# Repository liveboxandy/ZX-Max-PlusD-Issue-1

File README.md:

This is a recreation of the ZX Max Plus D Issue 1 PCB as designed by DonSuperfo but done in KiCAD 10.

This was only done in order to create an interactive BOM (in the BOM folder) to assist in the assembling of the PCB.

The KiCAD schematics 'should' be correct but nothing should be assumed as correct without checking with the original schematic and PCB layout. Although I have followed the original track and via layout further checking should be done before using these files to order a pcb with. Currently I would still order the pcb from PCBWay using the link from https://github.com/DonSuperfo/ZX-Max-128

Note that any part number for any device used in this project might not be the correct one from the original BOM as supplied from PCBWay as I had to change some parts to get a footprint that would fit in the space on the original pcb with the correct pin spacing. This required selecting a different part number or vendor. This applies mainly to capacitors. Some other parts are no longer available under that number from Digikey.

As always, measure twice and order one.

Use at your own risk.

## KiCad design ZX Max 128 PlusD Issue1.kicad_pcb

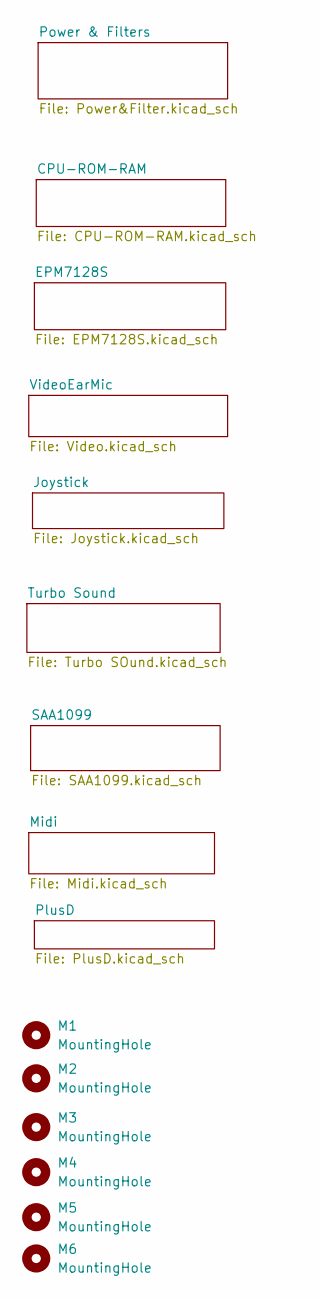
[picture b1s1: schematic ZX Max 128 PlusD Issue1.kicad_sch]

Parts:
M1, M2, M3, M4, M5, M6: MountingHole; MountingHole_3.2mm_M3_DIN965

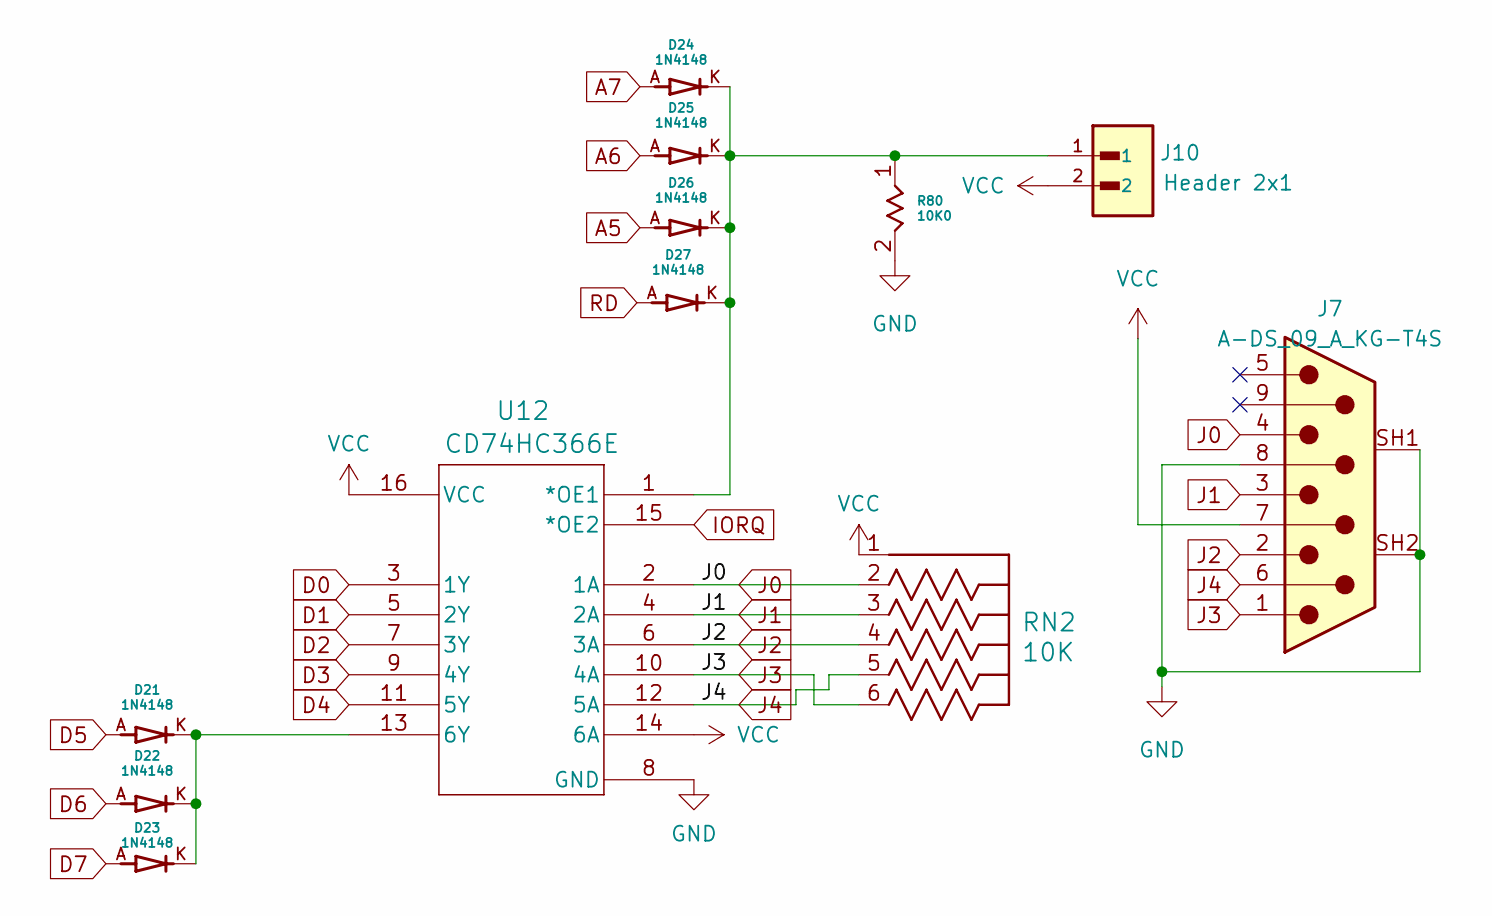
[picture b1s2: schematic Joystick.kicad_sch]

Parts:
D21, D22, D23, D24, D25, D26, D27: 1N4148; DIOAD753W49L380D172B; PARTREV 5
J7: A-DS_09_A_KG-T4S; ASSMANN_A-DS_09_A_KG-T4S; PARTREV 10
J10: Header 2x1; HARWIN_M20-9990246; PARTREV 14
R80: 10K0; STA_CF14_STP
RN2: 10K; 4606X-101-103LF
U12: CD74HC366E

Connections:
A5: D26.A; also elsewhere on the board
A6: D25.A; also elsewhere on the board
A7: D24.A; also elsewhere on the board
D0: U12.3 (1Y); also elsewhere on the board
D1: U12.5 (2Y); also elsewhere on the board
D2: U12.7 (3Y); also elsewhere on the board
D3: U12.9 (4Y); also elsewhere on the board
D4: U12.11 (5Y); also elsewhere on the board
D5: D21.A; also elsewhere on the board
D6: D22.A; also elsewhere on the board
D7: D23.A; also elsewhere on the board
GND: J7.8, J7.SH1, J7.SH2, R80.2, U12.8 (GND); also elsewhere on the board
IORQ: U12.15 (*OE2); also elsewhere on the board
J0: J7.4, RN2.2, U12.2 (1A)
J1: J7.3, RN2.3, U12.4 (2A)
J2: J7.2, RN2.4, U12.6 (3A)
J3: J7.1, RN2.6, U12.10 (4A)
J4: J7.6, RN2.5, U12.12 (5A)
unnamed: D21.K, D22.K, D23.K, U12.13 (6Y)
unnamed: D24.K, D25.K, D26.K, D27.K, J10.1, R80.1, U12.1 (*OE1)
RD: D27.A; also elsewhere on the board
VCC: J7.7, J10.2, RN2.1, U12.14 (6A), U12.16 (VCC); also elsewhere on the board

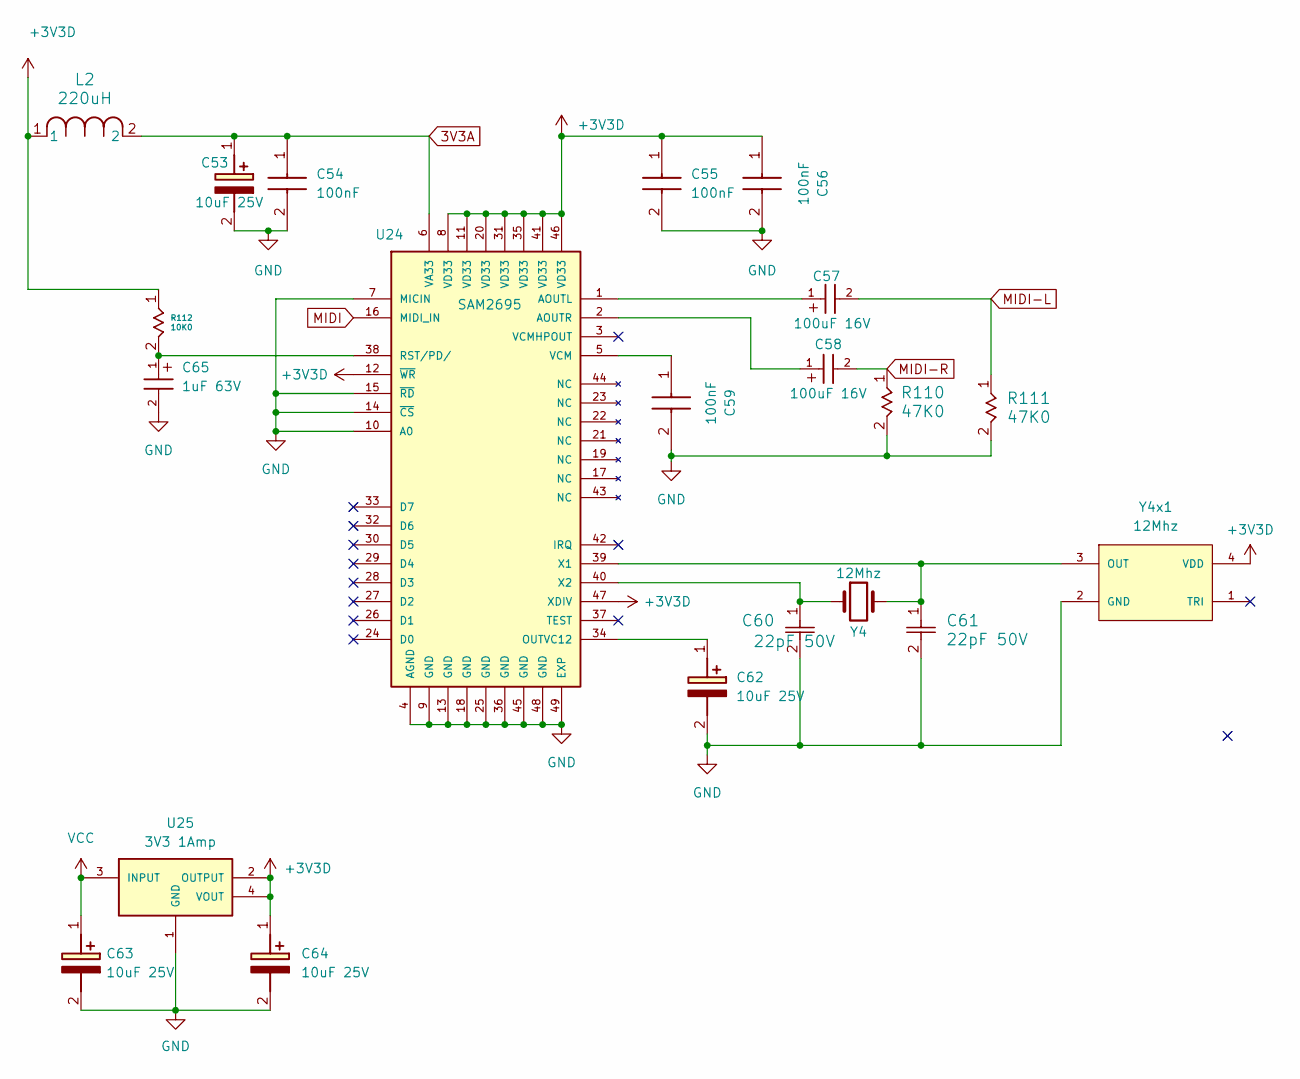
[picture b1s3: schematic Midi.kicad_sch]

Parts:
C53, C62, C63, C64: 10uF 25V; CAPPRD200W50D500H1100; Mouser Part Number 667-ECA-1EM100B
C54, C55, C56, C59: 100nF; CAPRB250W50L400T250H550; Mouser Part Number 594-K104Z15Y5VF5TL2
C57, C58: 100uF 16V; WCAP-ATG8_5X11_DXL_
C60, C61: 22pF 50V; CAP_K220J15C0GF53L2_VIS
C65: 1uF 63V; WCAP-ATG5_5X11_DXL_
L2: 220uH; IND_BOURNS_RLB0608
R110, R111: 47K0; STA_CF14_STP
R112: 10K0; STA_CF14_STP
U24: SAM2695; QFN40P600X600X90-49N; PARTREV N/A
U25: 3V3 1Amp; SOT230P700X185-4N
Y4: 12Mhz; Crystal_HC49-4H_Vertical
Y4x1: 12Mhz; OSC_ECS-2333-120-BN-TR

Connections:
3V3A: C53.1 (+), C54.1 (+), L2.2, U24.6 (VA33)
+3V3D: C55.1 (+), C56.1 (+), C64.1 (+), L2.1, R112.1, U24.8 (VD33), U24.11 (VD33), U24.12 (~WR), U24.20 (VD33), U24.31 (VD33), U24.35 (VD33), U24.41 (VD33), U24.46 (VD33), U24.47 (XDIV), U25.2 (OUTPUT), U25.4 (VOUT), Y4x1.4 (VDD); also elsewhere on the board
GND: C53.2 (-), C54.2 (-), C55.2 (-), C56.2 (-), C59.2 (-), C60.2, C61.2, C62.2 (-), C63.2 (-), C64.2 (-), C65.2, R110.2, R111.2, U24.4 (AGND), U24.7 (MICIN), U24.9 (GND), U24.10 (A0), U24.13 (GND), U24.14 (~CS), U24.15 (~RD), U24.18 (GND), U24.25 (GND), U24.36 (GND), U24.45 (GND), U24.48 (GND), U24.49 (EXP), U25.1 (GND), Y4x1.2 (GND); also elsewhere on the board
MIDI: U24.16 (MIDI_IN); also elsewhere on the board
MIDI-L: C57.2, R111.1; also elsewhere on the board
MIDI-R: C58.2, R110.1; also elsewhere on the board
unnamed: C59.1 (+), U24.5 (VCM)
unnamed: C62.1 (+), U24.34 (OUTVC12)
unnamed: C57.1, U24.1 (AOUTL)
unnamed: C58.1, U24.2 (AOUTR)
unnamed: C65.1, R112.2, U24.38 (RST/PD/)
unnamed: C61.1, U24.39 (X1), Y4.2, Y4x1.3 (OUT)
unnamed: C60.1, U24.40 (X2), Y4.1
VCC: C63.1 (+), U25.3 (INPUT); also elsewhere on the board

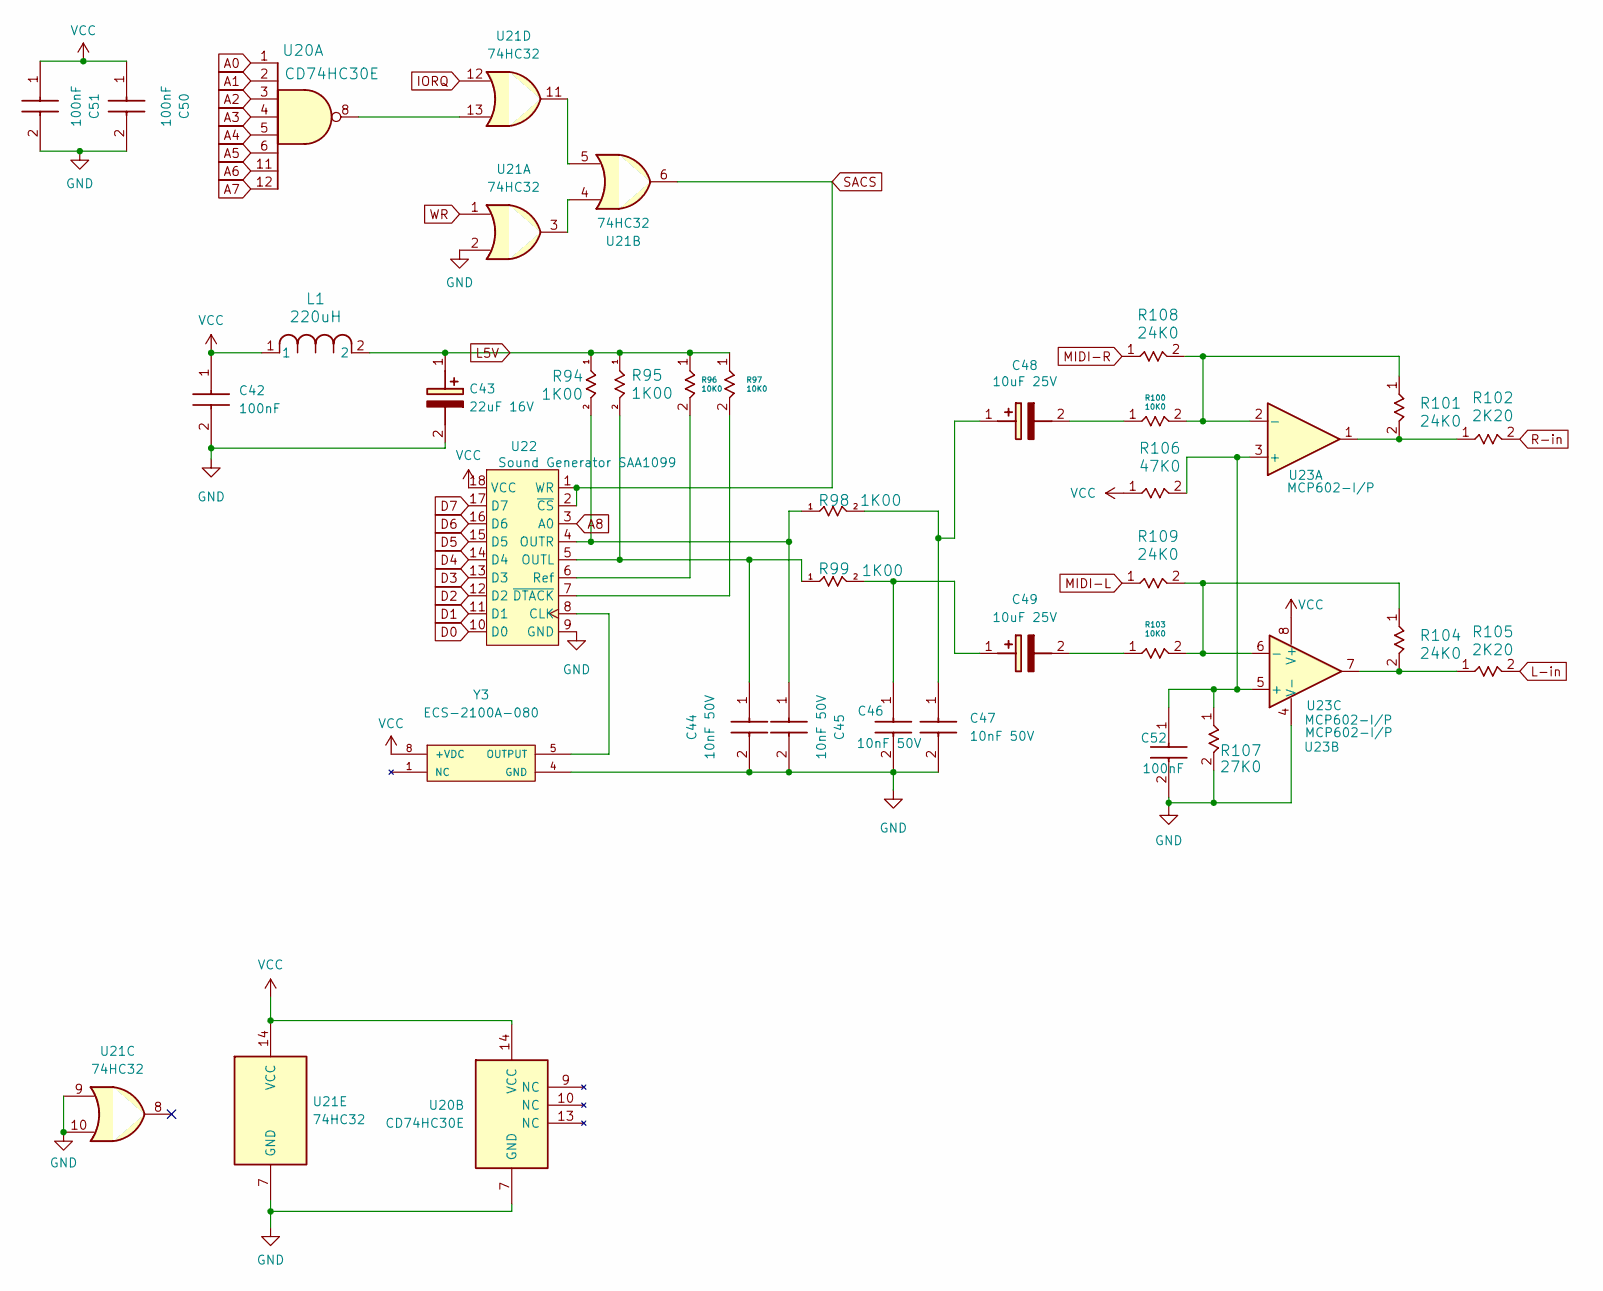
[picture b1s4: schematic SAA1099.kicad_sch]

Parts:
C42, C50, C51, C52: 100nF; CAPRB250W50L400T250H550; Mouser Part Number 594-K104Z15Y5VF5TL2
C43: 22uF 16V; CAPPRD200W50D500H1100; Mouser Part Number 667-ECA-1EM100B
C44, C45, C46, C47: 10nF 50V; CAPRB250W50L400T250H550; Mouser Part Number 594-K104Z15Y5VF5TL2
C48, C49: 10uF 25V; CAPPRD200W50D500H1100; Mouser Part Number 667-ECA-1EM100B
L1: 220uH; IND_BOURNS_RLB0608
R94, R95, R98, R99: 1K00; STA_CF14_STP
R96, R97, R100, R103: 10K0; STA_CF14_STP
R101, R104, R108, R109: 24K0; STA_CF14_STP
R102, R105: 2K20; STA_CF14_STP
R106: 47K0; STA_CF14_STP
R107: 27K0; STA_CF14_STP
U20: CD74HC30E; DIP794W53P254L1930H508Q14N
U21: 74HC32; DIP794W53P254L1930H508Q14N
U22: Sound Generator SAA1099; DIP-18_W7.62mm_Socket
U23: MCP602-I/P; DIP-8_W7.62mm_Socket
Y3: ECS-2100A-080; OSC_ECS-2100A-080; PARTREV N/A

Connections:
A0: U20.1; also elsewhere on the board
A1: U20.2; also elsewhere on the board
A2: U20.3; also elsewhere on the board
A3: U20.4; also elsewhere on the board
A4: U20.5; also elsewhere on the board
A5: U20.6; also elsewhere on the board
A6: U20.11; also elsewhere on the board
A7: U20.12; also elsewhere on the board
A8: U22.3 (A0); also elsewhere on the board
D0: U22.10 (D0); also elsewhere on the board
D1: U22.11 (D1); also elsewhere on the board
D2: U22.12 (D2); also elsewhere on the board
D3: U22.13 (D3); also elsewhere on the board
D4: U22.14 (D4); also elsewhere on the board
D5: U22.15 (D5); also elsewhere on the board
D6: U22.16 (D6); also elsewhere on the board
D7: U22.17 (D7); also elsewhere on the board
GND: C42.2 (-), C43.2 (-), C44.2 (-), C45.2 (-), C46.2 (-), C47.2 (-), C50.2 (-), C51.2 (-), C52.2 (-), R107.2, U20.7 (GND), U21.2, U21.7 (GND), U21.9, U21.10, U22.9 (GND), U23.4 (V-), Y3.4 (GND); also elsewhere on the board
IORQ: U21.12; also elsewhere on the board
L5V: C43.1 (+), L1.2, R94.1, R95.1, R96.1, R97.1
L-in: R105.2; also elsewhere on the board
MIDI-L: R109.1; also elsewhere on the board
MIDI-R: R108.1; also elsewhere on the board
unnamed: C44.1 (+), R95.2, R99.1, U22.5 (OUTL)
unnamed: C45.1 (+), R94.2, R98.1, U22.4 (OUTR)
unnamed: C46.1 (+), C49.1 (+), R99.2
unnamed: C47.1 (+), C48.1 (+), R98.2
unnamed: C48.2 (-), R100.1
unnamed: C49.2 (-), R103.1
unnamed: C52.1 (+), R106.2, R107.1, U23.3 (+), U23.5 (+)
unnamed: R101.2, R102.1, U23.1
unnamed: R104.2, R105.1, U23.7
unnamed: U20.8, U21.13
unnamed: U21.3, U21.4
unnamed: U21.5, U21.11
unnamed: U22.8 (CLK), Y3.5 (OUTPUT)
unnamed: R96.2, U22.6 (Ref)
unnamed: R97.2, U22.7 (~DTACK)
unnamed: R100.2, R101.1, R108.2, U23.2 (-)
unnamed: R103.2, R104.1, R109.2, U23.6 (-)
R-in: R102.2; also elsewhere on the board
SACS: U21.6, U22.1 (WR), U22.2 (~CS)
VCC: C42.1 (+), C50.1 (+), C51.1 (+), L1.1, R106.1, U20.14 (VCC), U21.14 (VCC), U22.18 (VCC), U23.8 (V+), Y3.8 (+VDC); also elsewhere on the board
WR: U21.1; also elsewhere on the board

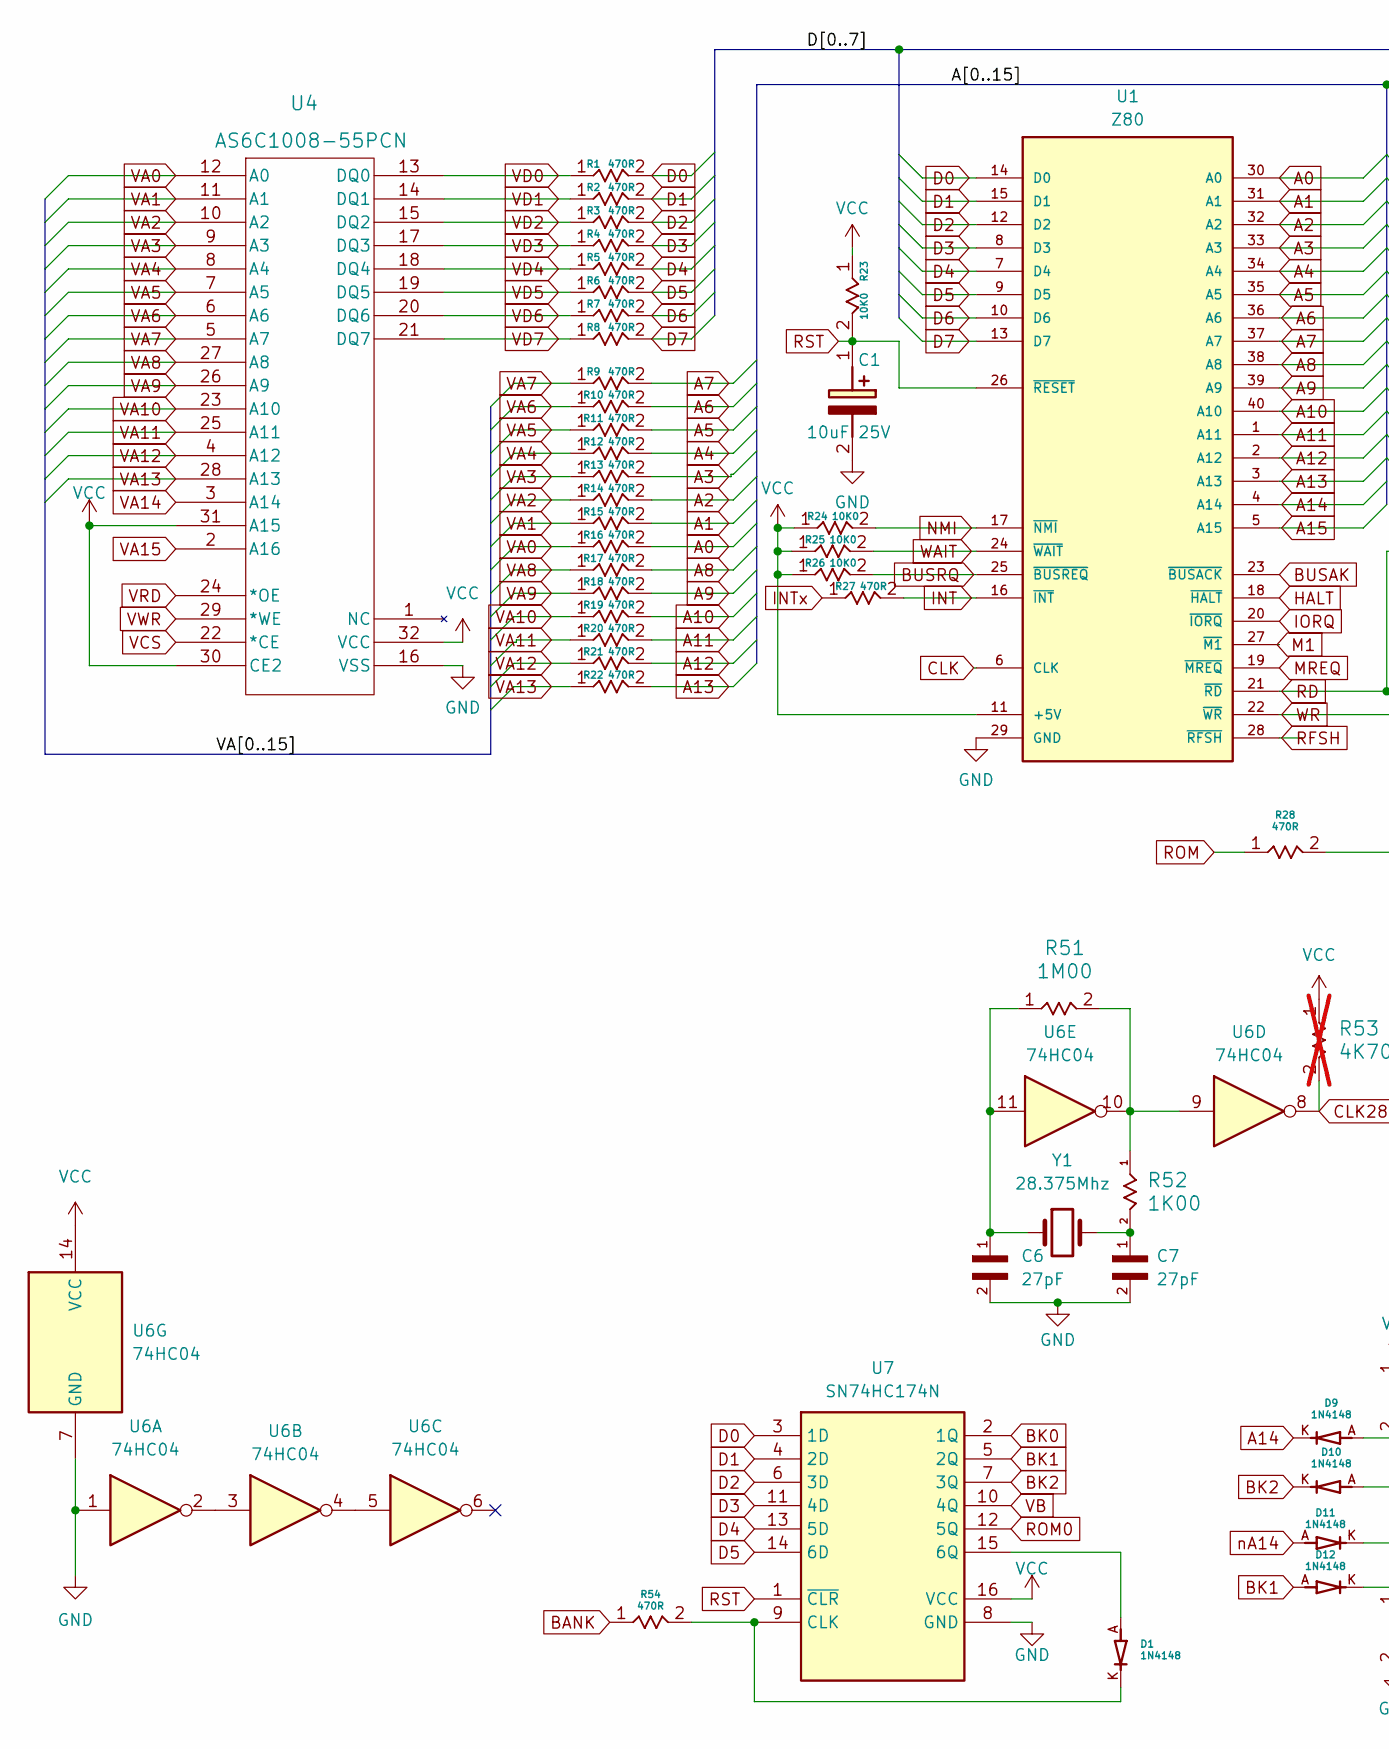
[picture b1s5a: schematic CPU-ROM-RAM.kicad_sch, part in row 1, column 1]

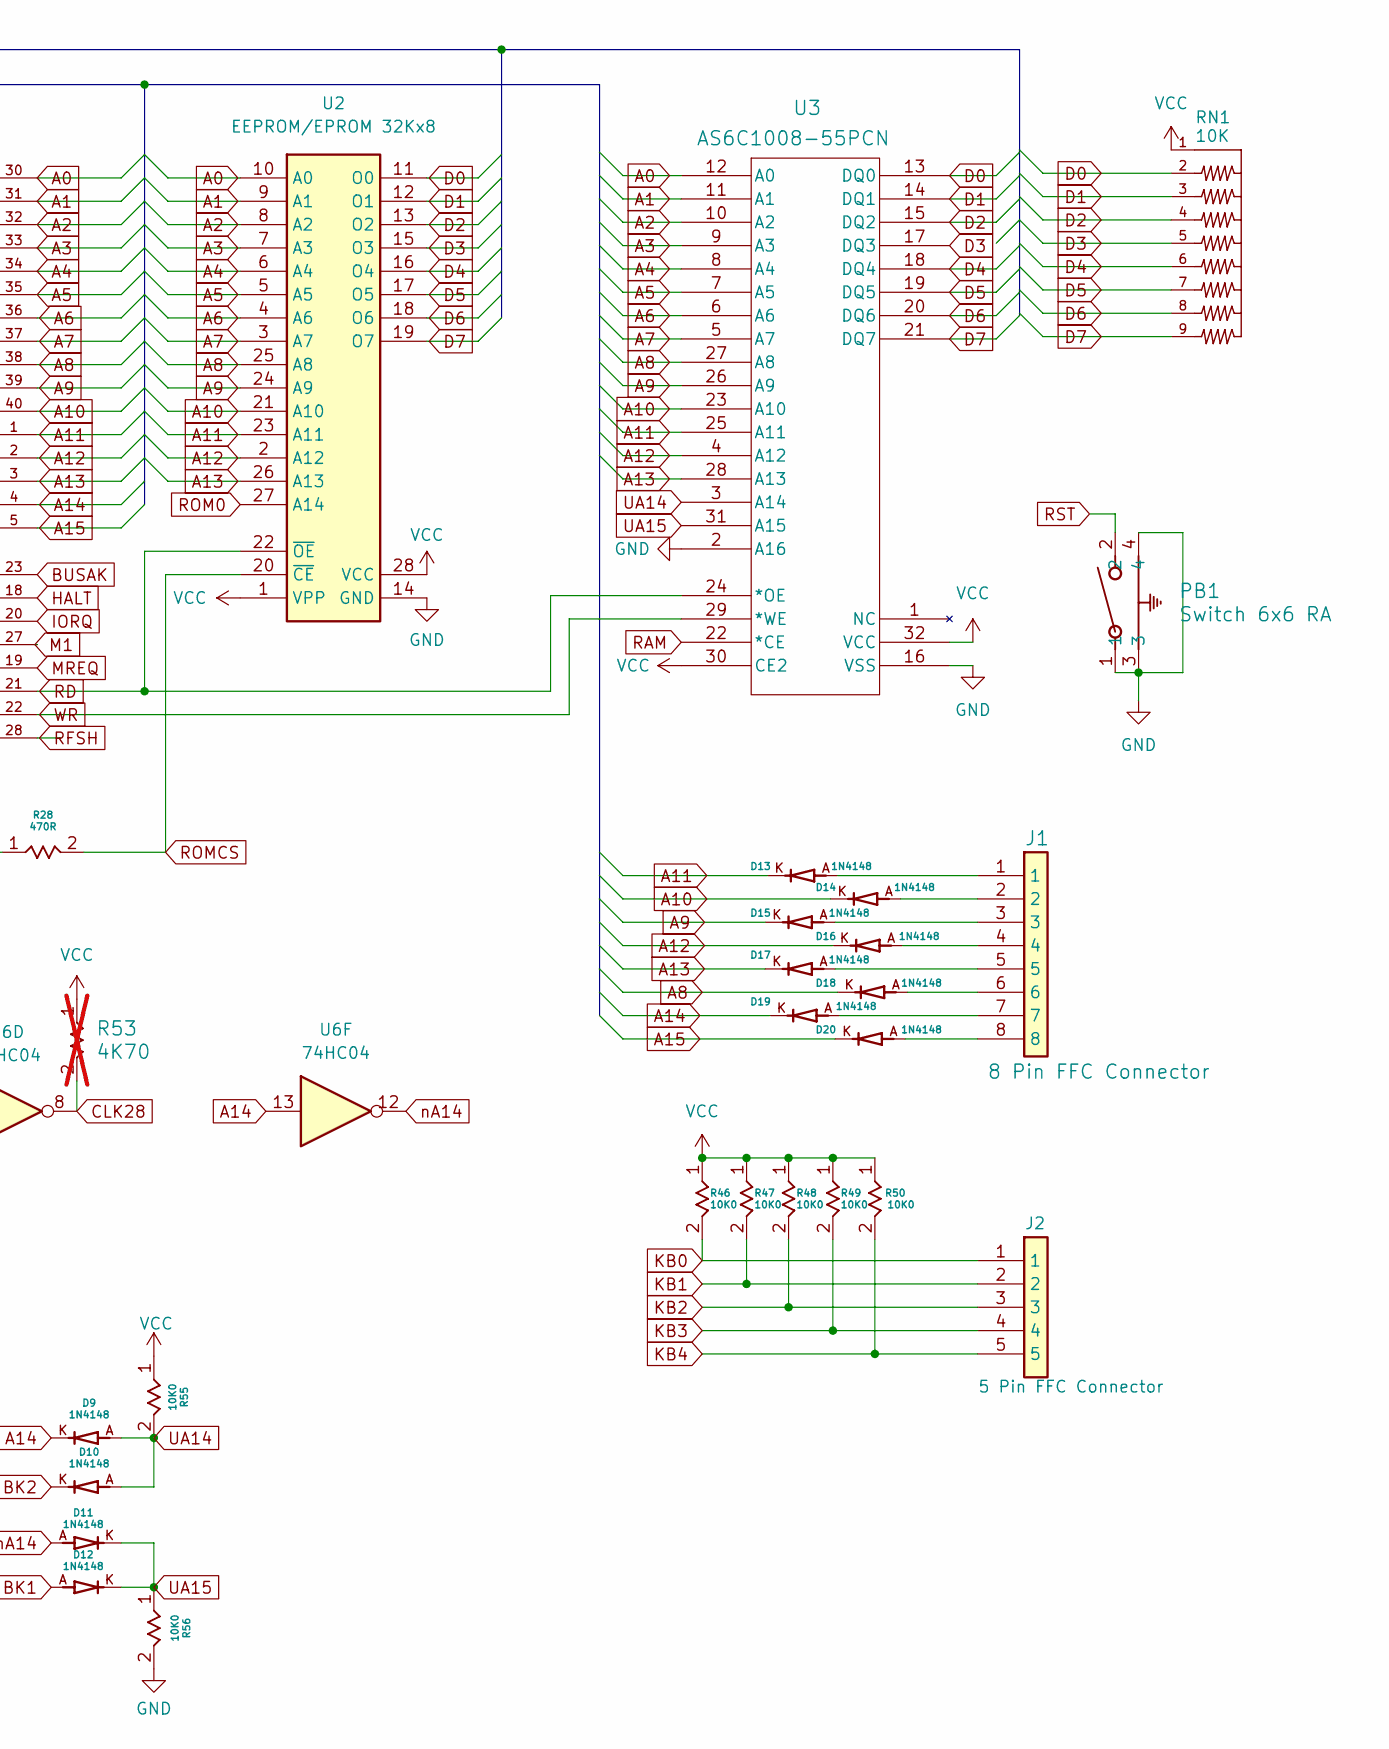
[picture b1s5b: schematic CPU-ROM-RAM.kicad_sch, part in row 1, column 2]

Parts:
C1: 10uF 25V; CAPPRD200W50D500H1100; Mouser Part Number 667-ECA-1EM100B
C6, C7: 27pF; CAPRB250W50L400T250H550; PARTREV 20200310
D1, D9, D10, D11, D12, D13, D14, D15, D16, D17, D18, D19, D20: 1N4148; DIOAD753W49L380D172B; PARTREV 5
J1: 8 Pin FFC Connector; 55203155
J2: 5 Pin FFC Connector; 55203155; Mouser Part Number 571-5-520315-5
PB1: Switch 6x6 RA; SW2_1825027-G_TEC
R1, R2, R3, R4, R5, R6, R7, R8, R9, R10, R11, R12, R13, R14, R15, R16, R17, R18, R19, R20, R21, R22, R27, R28, R54: 470R; STA_CF14_STP
R23, R24, R25, R26, R46, R47, R48, R49, R50, R55, R56: 10K0; STA_CF14_STP
R51: 1M00; STA_CF14_STP
R52: 1K00; STA_CF14_STP
R53: 4K70; STA_CF14_STP; not fitted
RN1: 10K; SIP249W50P254L2281H508Q9; PARTREV 10/1/20
U1: Z80; Z80_Socket
U2: EEPROM/EPROM 32Kx8; DIP1556W56P254L3702H483Q28N; Mouser Part Number 556-AT27C256R-45PU
U3, U4: AS6C1008-55PCN; PDIP-32_MIL600_ALL
U6: 74HC04; DIP794W53P254L1930H508Q14N
U7: SN74HC174N; DIP794W53P254L1930H508Q16N; Mouser Part Number 595-SN74HC174N
Y1: 28.375Mhz; Crystal_HC49-4H_Vertical

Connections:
A0: R16.2, U1.30 (A0), U2.10 (A0), U3.12 (A0); also elsewhere on the board
A1: R15.2, U1.31 (A1), U2.9 (A1), U3.11 (A1); also elsewhere on the board
A2: R14.2, U1.32 (A2), U2.8 (A2), U3.10 (A2); also elsewhere on the board
A3: R13.2, U1.33 (A3), U2.7 (A3), U3.9 (A3); also elsewhere on the board
A4: R12.2, U1.34 (A4), U2.6 (A4), U3.8 (A4); also elsewhere on the board
A5: R11.2, U1.35 (A5), U2.5 (A5), U3.7 (A5); also elsewhere on the board
A6: R10.2, U1.36 (A6), U2.4 (A6), U3.6 (A6); also elsewhere on the board
A7: R9.2, U1.37 (A7), U2.3 (A7), U3.5 (A7); also elsewhere on the board
A8: D18.K, R17.2, U1.38 (A8), U2.25 (A8), U3.27 (A8); also elsewhere on the board
A9: D15.K, R18.2, U1.39 (A9), U2.24 (A9), U3.26 (A9); also elsewhere on the board
A10: D14.K, R19.2, U1.40 (A10), U2.21 (A10), U3.23 (A10); also elsewhere on the board
A11: D13.K, R20.2, U1.1 (A11), U2.23 (A11), U3.25 (A11); also elsewhere on the board
A12: D16.K, R21.2, U1.2 (A12), U2.2 (A12), U3.4 (A12); also elsewhere on the board
A13: D17.K, R22.2, U1.3 (A13), U2.26 (A13), U3.28 (A13); also elsewhere on the board
A14: D9.K, D19.K, U1.4 (A14), U6.13; also elsewhere on the board
A15: D20.K, U1.5 (A15); also elsewhere on the board
BANK: R54.1; also elsewhere on the board
BK0: U7.2 (1Q); also elsewhere on the board
BK1: D12.A, U7.5 (2Q); also elsewhere on the board
BK2: D10.K, U7.7 (3Q); also elsewhere on the board
BUSAK: U1.23 (~BUSACK); also elsewhere on the board
BUSRQ: R26.2, U1.25 (~BUSREQ); also elsewhere on the board
CLK: U1.6 (CLK); also elsewhere on the board
CLK28: R53.2, U6.8; also elsewhere on the board
D0: R1.2, RN1.2, U1.14 (D0), U2.11 (O0), U3.13 (DQ0), U7.3 (1D); also elsewhere on the board
D1: R2.2, RN1.3, U1.15 (D1), U2.12 (O1), U3.14 (DQ1), U7.4 (2D); also elsewhere on the board
D2: R3.2, RN1.4, U1.12 (D2), U2.13 (O2), U3.15 (DQ2), U7.6 (3D); also elsewhere on the board
D3: R4.2, RN1.5, U1.8 (D3), U2.15 (O3), U3.17 (DQ3), U7.11 (4D); also elsewhere on the board
D4: R5.2, RN1.6, U1.7 (D4), U2.16 (O4), U3.18 (DQ4), U7.13 (5D); also elsewhere on the board
D5: R6.2, RN1.7, U1.9 (D5), U2.17 (O5), U3.19 (DQ5), U7.14 (6D); also elsewhere on the board
D6: R7.2, RN1.8, U1.10 (D6), U2.18 (O6), U3.20 (DQ6); also elsewhere on the board
D7: R8.2, RN1.9, U1.13 (D7), U2.19 (O7), U3.21 (DQ7); also elsewhere on the board
GND: C1.2 (-), C6.2, C7.2, PB1.1, PB1.3, PB1.4, R56.2, U1.29 (GND), U2.14 (GND), U3.2 (A16), U3.16 (VSS), U4.16 (VSS), U6.1, U6.7 (GND), U7.8 (GND); also elsewhere on the board
HALT: U1.18 (~HALT); also elsewhere on the board
INT: R27.2, U1.16 (~INT); also elsewhere on the board
INTx: R27.1; also elsewhere on the board
IORQ: U1.20 (~IORQ); also elsewhere on the board
KB0: J2.1, R46.2; also elsewhere on the board
KB1: J2.2, R47.2; also elsewhere on the board
KB2: J2.3, R48.2; also elsewhere on the board
KB3: J2.4, R49.2; also elsewhere on the board
KB4: J2.5, R50.2; also elsewhere on the board
M1: U1.27 (~M1); also elsewhere on the board
MREQ: U1.19 (~MREQ); also elsewhere on the board
NMI: R24.2, U1.17 (~NMI); also elsewhere on the board
unnamed: C6.1, R51.1, U6.11, Y1.1
unnamed: C7.1, R52.2, Y1.2
unnamed: D13.A, J1.1
unnamed: D14.A, J1.2
unnamed: D15.A, J1.3
unnamed: D16.A, J1.4
unnamed: D17.A, J1.5
unnamed: D18.A, J1.6
unnamed: D19.A, J1.7
unnamed: D20.A, J1.8
unnamed: R51.2, R52.1, U6.9, U6.10
unnamed: U6.2, U6.3
unnamed: U6.4, U6.5
unnamed: D1.A, U7.15 (6Q)
unnamed: D1.K, R54.2, U7.9 (CLK)
RAM: U3.22 (*CE); also elsewhere on the board
RD: U1.21 (~RD), U2.22 (~OE), U3.24 (*OE); also elsewhere on the board
RFSH: U1.28 (~RFSH); also elsewhere on the board
ROM: R28.1; also elsewhere on the board
ROM0: U2.27 (A14), U7.12 (5Q)
ROMCS: R28.2, U2.20 (~CE); also elsewhere on the board
RST: C1.1 (+), PB1.2, R23.2, U1.26 (~RESET), U7.1 (~CLR); also elsewhere on the board
UA14: D9.A, D10.A, R55.2, U3.3 (A14)
UA15: D11.K, D12.K, R56.1, U3.31 (A15)
VA0: R16.1, U4.12 (A0); also elsewhere on the board
VA1: R15.1, U4.11 (A1); also elsewhere on the board
VA2: R14.1, U4.10 (A2); also elsewhere on the board
VA3: R13.1, U4.9 (A3); also elsewhere on the board
VA4: R12.1, U4.8 (A4); also elsewhere on the board
VA5: R11.1, U4.7 (A5); also elsewhere on the board
VA6: R10.1, U4.6 (A6); also elsewhere on the board
VA7: R9.1, U4.5 (A7); also elsewhere on the board
VA8: R17.1, U4.27 (A8); also elsewhere on the board
VA9: R18.1, U4.26 (A9); also elsewhere on the board
VA10: R19.1, U4.23 (A10); also elsewhere on the board
VA11: R20.1, U4.25 (A11); also elsewhere on the board
VA12: R21.1, U4.4 (A12); also elsewhere on the board
VA13: R22.1, U4.28 (A13); also elsewhere on the board
VA14: U4.3 (A14); also elsewhere on the board
VA15: U4.2 (A16); also elsewhere on the board
VB: U7.10 (4Q); also elsewhere on the board
VCC: R23.1, R24.1, R25.1, R26.1, R46.1, R47.1, R48.1, R49.1, R50.1, R53.1, R55.1, RN1.1, U1.11 (+5V), U2.1 (VPP), U2.28 (VCC), U3.30 (CE2), U3.32 (VCC), U4.30 (CE2), U4.31 (A15), U4.32 (VCC), U6.14 (VCC), U7.16 (VCC); also elsewhere on the board
VCS: U4.22 (*CE); also elsewhere on the board
VD0: R1.1, U4.13 (DQ0); also elsewhere on the board
VD1: R2.1, U4.14 (DQ1); also elsewhere on the board
VD2: R3.1, U4.15 (DQ2); also elsewhere on the board
VD3: R4.1, U4.17 (DQ3); also elsewhere on the board
VD4: R5.1, U4.18 (DQ4); also elsewhere on the board
VD5: R6.1, U4.19 (DQ5); also elsewhere on the board
VD6: R7.1, U4.20 (DQ6); also elsewhere on the board
VD7: R8.1, U4.21 (DQ7); also elsewhere on the board
VRD: U4.24 (*OE); also elsewhere on the board
VWR: U4.29 (*WE); also elsewhere on the board
WAIT: R25.2, U1.24 (~WAIT); also elsewhere on the board
WR: U1.22 (~WR), U3.29 (*WE); also elsewhere on the board
nA14: D11.A, U6.12

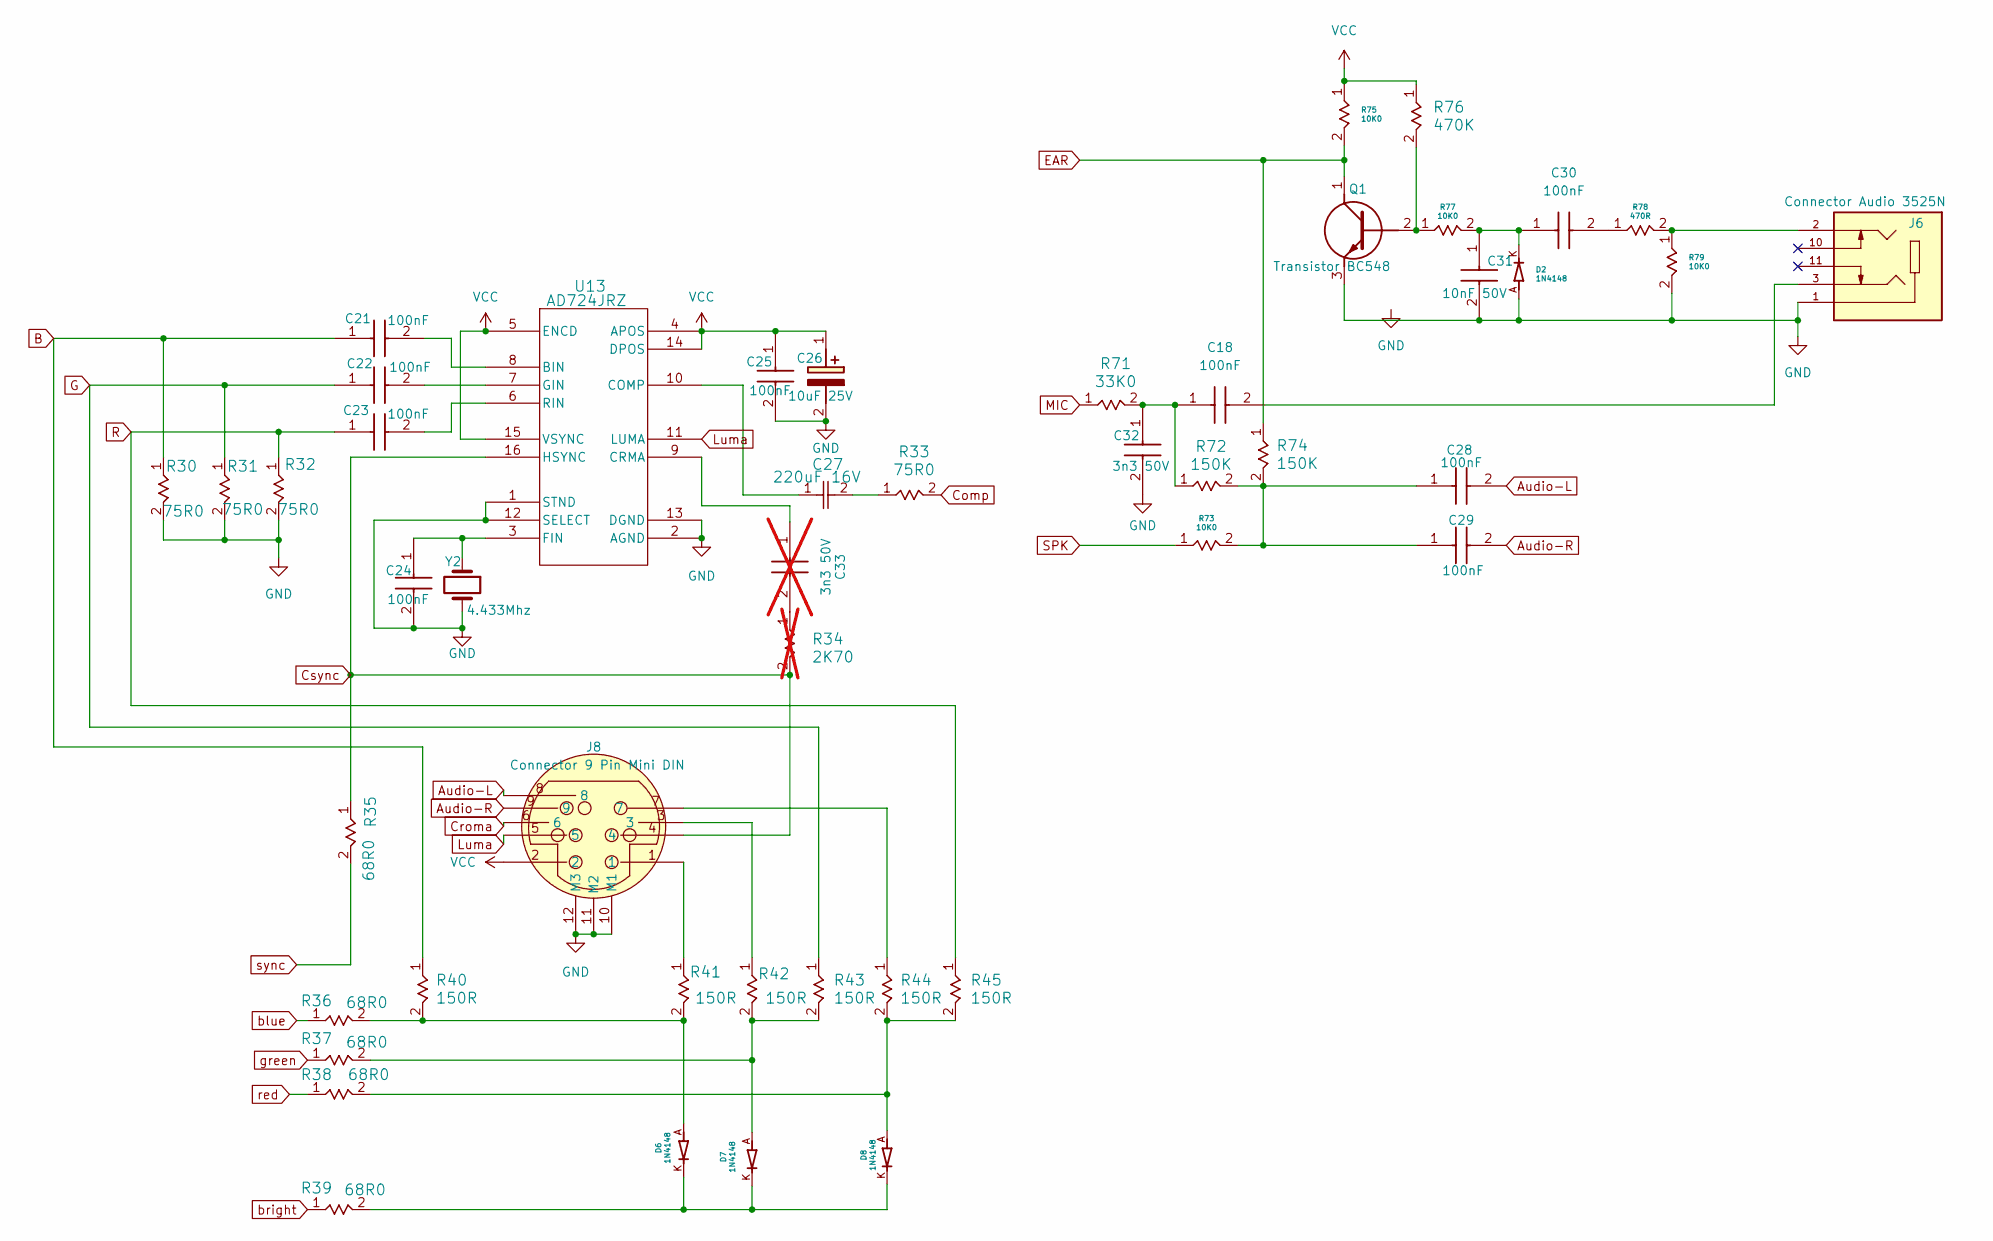
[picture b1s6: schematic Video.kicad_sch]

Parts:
C18, C21, C22, C23, C24, C25, C28, C29, C30: 100nF; CAPRB250W50L400T250H550; Mouser Part Number 594-K104Z15Y5VF5TL2
C26: 10uF 25V; CAPPRD200W50D500H1100; Mouser Part Number 667-ECA-1EM100B
C27: 220uF 16V; CAPPRD200W50D500H1100
C31: 10nF 50V; CAPRB250W50L400T250H550; Mouser Part Number 594-K104Z15Y5VF5TL2
C32: 3n3 50V; CAPRB250W50L400T250H550; Mouser Part Number 594-K104Z15Y5VF5TL2
C33: 3n3 50V; CAPRB250W50L400T250H550; Mouser Part Number 594-K104Z15Y5VF5TL2; not fitted
D2, D6, D7, D8: 1N4148; DIOAD753W49L380D172B; PARTREV 5
J6: Connector Audio 3525N; CUI_SJ1-3525N
J8: Connector 9 Pin Mini DIN; KMDGX9SBS1; Mouser Part Number 806-KMDGX-9S-BS-1
Q1: Transistor BC548; BC548BTA
R30, R31, R32, R33: 75R0; STA_CF14_STP
R34: 2K70; STA_CF14_STP; not fitted
R35, R36, R37, R38, R39: 68R0; STA_CF14_STP
R40, R41, R42, R43, R44, R45: 150R; STA_CF14_STP
R71: 33K0; STA_CF14_STP
R72, R74: 150K; STA_CF14_STP
R73, R75, R77, R79: 10K0; STA_CF14_STP
R76: 470K; STA_CF14_STP
R78: 470R; STA_CF14_STP
U13: AD724JRZ; RW_16_ADI
Y2: 4.433Mhz; Crystal_HC49-4H_Vertical

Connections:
Audio-L: C28.2 (-), J8.8; also elsewhere on the board
Audio-R: C29.2 (-), J8.9; also elsewhere on the board
B: C21.1 (+), R30.1, R40.1
Comp: R33.2; also elsewhere on the board
Croma: J8.6
Csync: J8.4, R34.2, R35.1, U13.16 (HSYNC)
EAR: Q1.1 (C), R74.1, R75.2; also elsewhere on the board
G: C22.1 (+), R31.1, R43.1
GND: C24.2 (-), C25.2 (-), C26.2 (-), C31.2 (-), C32.2 (-), D2.A, J6.1, J8.10 (MH1), J8.11 (MH2), J8.12 (MH3), Q1.3 (E), R30.2, R31.2, R32.2, R79.2, U13.1 (STND), U13.2 (AGND), U13.12 (SELECT), U13.13 (DGND), Y2.2; also elsewhere on the board
Luma: J8.5, U13.11 (LUMA)
MIC: R71.1; also elsewhere on the board
unnamed: C18.1 (+), C32.1 (+), R71.2, R72.1
unnamed: C18.2 (-), J6.3
unnamed: C21.2 (-), U13.8 (BIN)
unnamed: C22.2 (-), U13.7 (GIN)
unnamed: C23.2 (-), U13.6 (RIN)
unnamed: C24.1 (+), U13.3 (FIN), Y2.1
unnamed: C27.2, R33.1
unnamed: C28.1 (+), C29.1 (+), R72.2, R73.2, R74.2
unnamed: C30.1 (+), C31.1 (+), D2.K, R77.2
unnamed: C30.2 (-), R78.1
unnamed: C33.1 (+), U13.9 (CRMA)
unnamed: C33.2 (-), R34.1
unnamed: D6.A, R36.2, R40.2, R41.2
unnamed: D6.K, D7.K, D8.K, R39.2
unnamed: D7.A, R37.2, R42.2, R43.2
unnamed: D8.A, R38.2, R44.2, R45.2
unnamed: J6.2, R78.2, R79.1
unnamed: J8.1, R41.1
unnamed: J8.3, R42.1
unnamed: J8.7, R44.1
unnamed: Q1.2 (B), R76.2, R77.1
unnamed: C27.1, U13.10 (COMP)
R: C23.1 (+), R32.1, R45.1
SPK: R73.1; also elsewhere on the board
VCC: C25.1 (+), C26.1 (+), J8.2, R75.1, R76.1, U13.4 (APOS), U13.5 (ENCD), U13.14 (DPOS), U13.15 (VSYNC); also elsewhere on the board
blue: R36.1; also elsewhere on the board
bright: R39.1; also elsewhere on the board
green: R37.1; also elsewhere on the board
red: R38.1; also elsewhere on the board
sync: R35.2; also elsewhere on the board
